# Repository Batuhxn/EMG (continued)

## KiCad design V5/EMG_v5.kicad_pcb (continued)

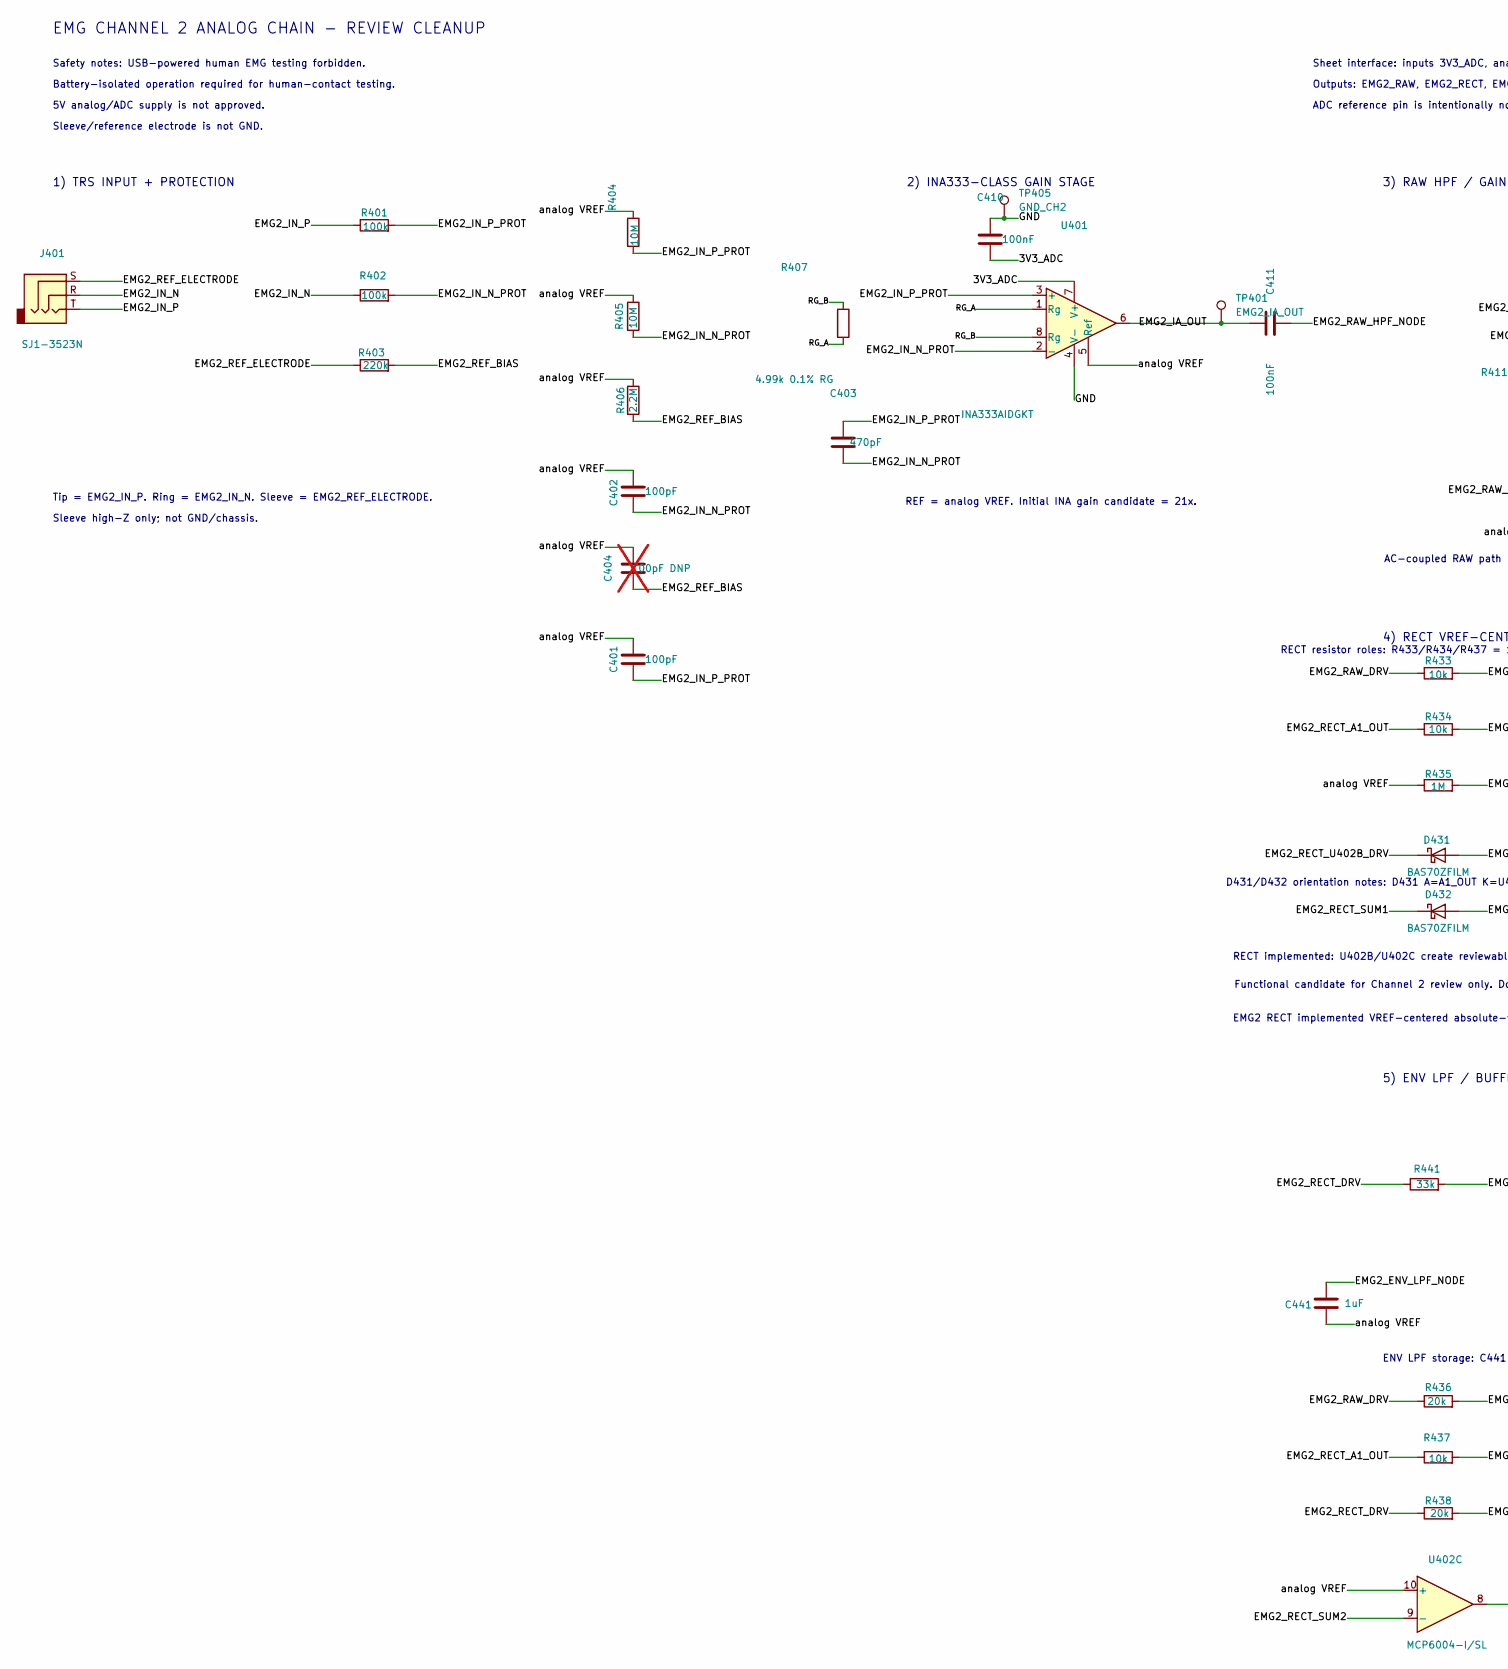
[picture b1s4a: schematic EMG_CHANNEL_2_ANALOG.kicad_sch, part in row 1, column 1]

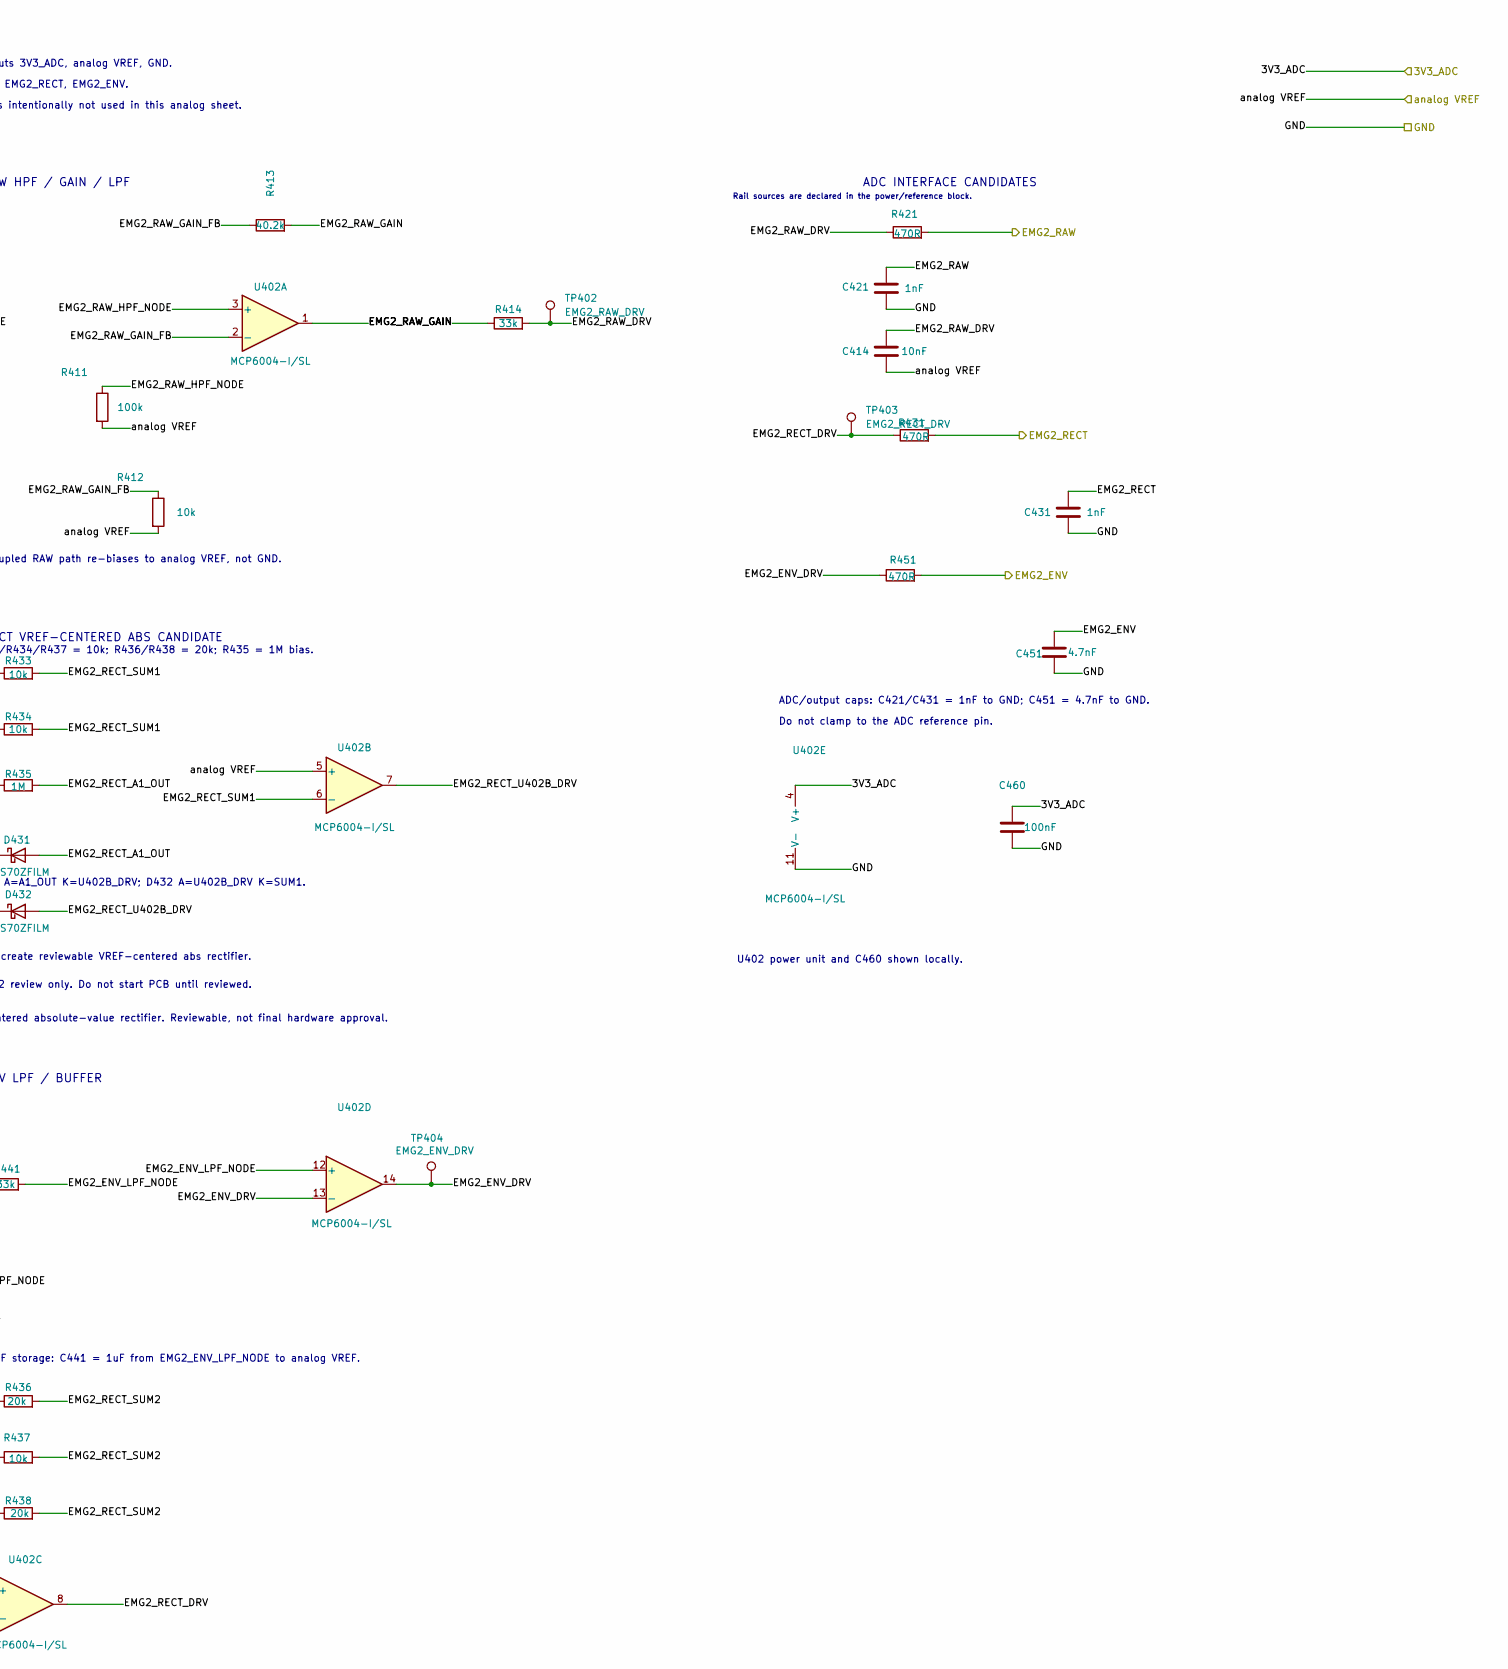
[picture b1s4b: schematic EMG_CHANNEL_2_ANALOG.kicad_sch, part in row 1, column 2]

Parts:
C401, C402: 100pF; C_0603_1608Metric
C403: 470pF; C_0603_1608Metric
C404: 100pF DNP; C_0603_1608Metric; not fitted
C410, C411: 100nF; C_0603_1608Metric
C414: 10nF; C_0603_1608Metric
C421, C431: 1nF; C_0805_2012Metric
C441: 1uF; C_0805_2012Metric
C451: 4.7nF; C_0805_2012Metric
C460: 100nF; C_0805_2012Metric
D431, D432: BAS70ZFILM; D_SOD-123
J401: SJ1-3523N; Jack_3.5mm_CUI_SJ1-3523N_Horizontal
R401, R402: 100k; R_1206_3216Metric
R403: 220k; R_1206_3216Metric
R404, R405: 10M; R_1206_3216Metric
R406: 2.2M; R_1206_3216Metric
R407: 4.99k 0.1% RG; R_0805_2012Metric
R411: 100k; R_0805_2012Metric
R412, R433, R434, R437: 10k; R_0805_2012Metric
R413: 40.2k; R_0805_2012Metric
R414, R441: 33k; R_0805_2012Metric
R421, R431, R451: 470R; R_0805_2012Metric
R435: 1M; R_0805_2012Metric
R436, R438: 20k; R_0805_2012Metric
TP401: EMG2_IA_OUT; TestPoint_Pad_D1.5mm
TP402: EMG2_RAW_DRV; TestPoint_Pad_D1.5mm
TP403: EMG2_RECT_DRV; TestPoint_Pad_D1.5mm
TP404: EMG2_ENV_DRV; TestPoint_Pad_D1.5mm
TP405: GND_CH2; TestPoint_Pad_D2.0mm
U401: INA333AIDGKT; INA333_DGK_VSSOP-8_TI
U402: MCP6004-I/SL; SOIC-14_3.9x8.7mm_P1.27mm

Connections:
/EMG_CHANNEL_1_ANALOG/3V3_ADC: C410.2, C460.1, U401.7 (V+), U402.4 (V+); also elsewhere on the board
/EMG_CHANNEL_1_ANALOG/analog VREF: C401.1, C402.1, C404.1, C414.2, C441.2, R404.1, R405.1, R406.1, R411.2, R412.2, R435.1, U401.5 (Ref), U402.5 (+), U402.10 (+); also elsewhere on the board
/EMG_CHANNEL_2_ANALOG/EMG2_ENV: C451.1, R451.2; also elsewhere on the board
/EMG_CHANNEL_2_ANALOG/EMG2_ENV_DRV: R451.1, TP404.1 (1_1), U402.13 (-), U402.14
/EMG_CHANNEL_2_ANALOG/EMG2_ENV_LPF_NODE: C441.1, R441.2, U402.12 (+)
/EMG_CHANNEL_2_ANALOG/EMG2_IA_OUT: C411.1, TP401.1 (1_1), U401.6
/EMG_CHANNEL_2_ANALOG/EMG2_IN_N: J401.R, R402.1
/EMG_CHANNEL_2_ANALOG/EMG2_IN_N_PROT: C402.2, C403.2, R402.2, R405.2, U401.2 (-)
/EMG_CHANNEL_2_ANALOG/EMG2_IN_P: J401.T, R401.1
/EMG_CHANNEL_2_ANALOG/EMG2_IN_P_PROT: C401.2, C403.1, R401.2, R404.2, U401.3 (+)
/EMG_CHANNEL_2_ANALOG/EMG2_RAW: C421.1, R421.2; also elsewhere on the board
/EMG_CHANNEL_2_ANALOG/EMG2_RAW_DRV: C414.1, R414.2, R421.1, R433.1, R436.1, TP402.1 (1_1)
/EMG_CHANNEL_2_ANALOG/EMG2_RAW_GAIN: R413.2, R414.1, U402.1
/EMG_CHANNEL_2_ANALOG/EMG2_RAW_GAIN_FB: R412.1, R413.1, U402.2 (-)
/EMG_CHANNEL_2_ANALOG/EMG2_RAW_HPF_NODE: C411.2, R411.1, U402.3 (+)
/EMG_CHANNEL_2_ANALOG/EMG2_RECT: C431.1, R431.2; also elsewhere on the board
/EMG_CHANNEL_2_ANALOG/EMG2_RECT_A1_OUT: D431.2 (A), R434.1, R435.2, R437.1
/EMG_CHANNEL_2_ANALOG/EMG2_RECT_DRV: R431.1, R438.1, R441.1, TP403.1 (1_1), U402.8
/EMG_CHANNEL_2_ANALOG/EMG2_RECT_SUM1: D432.1 (K), R433.2, R434.2, U402.6 (-)
/EMG_CHANNEL_2_ANALOG/EMG2_RECT_SUM2: R436.2, R437.2, R438.2, U402.9 (-)
/EMG_CHANNEL_2_ANALOG/EMG2_RECT_U402B_DRV: D431.1 (K), D432.2 (A), U402.7
/EMG_CHANNEL_2_ANALOG/EMG2_REF_BIAS: C404.2, R403.2, R406.2
/EMG_CHANNEL_2_ANALOG/EMG2_REF_ELECTRODE: J401.S, R403.1
/EMG_CHANNEL_2_ANALOG/RG_A: R407.2, U401.1 (Rg)
/EMG_CHANNEL_2_ANALOG/RG_B: R407.1, U401.8 (Rg)
GND: C410.1, C421.2, C431.2, C451.2, C460.2, TP405.1 (1_1), U401.4 (V-), U402.11 (V-); also elsewhere on the board

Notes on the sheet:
EMG CHANNEL 2 ANALOG CHAIN - REVIEW CLEANUP
Safety notes: USB-powered human EMG testing forbidden.
Battery-isolated operation required for human-contact testing.
5V analog/ADC supply is not approved.
Sleeve/reference electrode is not GND.
Sheet interface: inputs 3V3_ADC, analog VREF, GND.
Outputs: EMG2_RAW, EMG2_RECT, EMG2_ENV.
ADC reference pin is intentionally not used in this analog sheet.
Rail sources are declared in the power/reference block.
1) TRS INPUT + PROTECTION
Tip = EMG2_IN_P. Ring = EMG2_IN_N. Sleeve = EMG2_REF_ELECTRODE.
Sleeve high-Z only; not GND/chassis.
2) INA333-CLASS GAIN STAGE
REF = analog VREF. Initial INA gain candidate = 21x.
3) RAW HPF / GAIN / LPF
AC-coupled RAW path re-biases to analog VREF, not GND.
4) RECT VREF-CENTERED ABS CANDIDATE
RECT implemented: U402B/U402C create reviewable VREF-centered abs rectifier.
Functional candidate for Channel 2 review only. Do not start PCB until reviewed.
5) ENV LPF / BUFFER
ENV LPF storage: C441 = 1uF from EMG2_ENV_LPF_NODE to analog VREF.
U402 power unit and C460 shown locally.
ADC INTERFACE CANDIDATES
ADC/output caps: C421/C431 = 1nF to GND; C451 = 4.7nF to GND.
Do not clamp to the ADC reference pin.
D431/D432 orientation notes: D431 A=A1_OUT K=U402B_DRV; D432 A=U402B_DRV K=SUM1.
RECT resistor roles: R433/R434/R437 = 10k; R436/R438 = 20k; R435 = 1M bias.
EMG2 RECT implemented VREF-centered absolute-value rectifier. Reviewable, not final hardware approval.

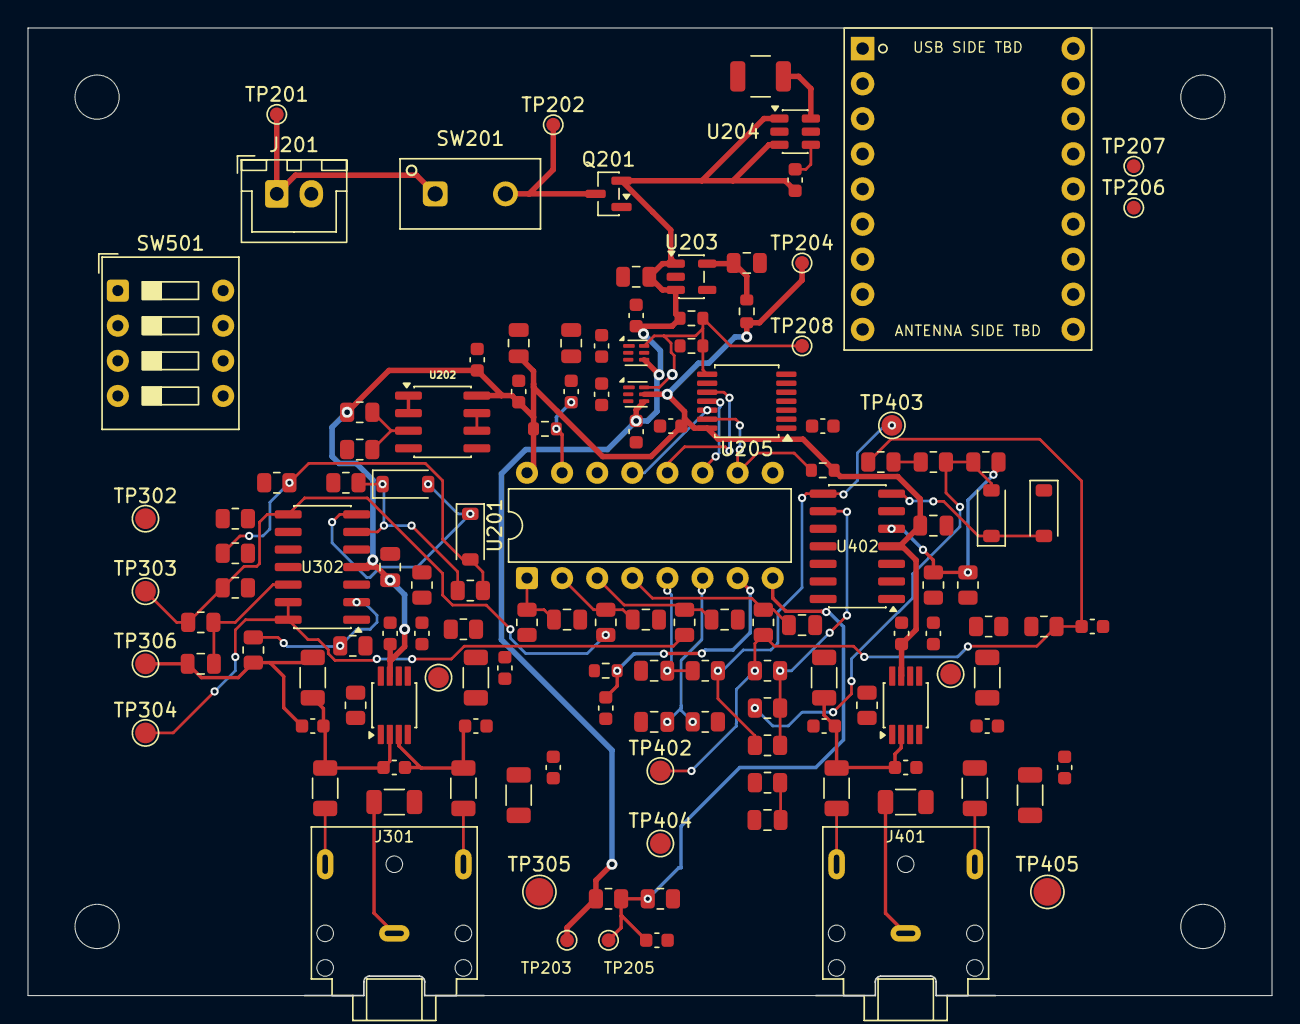
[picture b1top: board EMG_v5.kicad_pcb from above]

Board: 2 copper layers, 90.0 x 70.0 mm, 134 parts (0 on the bottom side), 76 nets.

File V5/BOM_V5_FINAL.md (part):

# EMG V5 Final Purchasing BOM

> Source of truth: `V5/EMG_v5.kicad_pcb` and related current schematics/documentation on branch `v5/KiCad`. Price/stock snapshot: **2026-08-10**. The old `BOM_V5_DRAFT.md` was used only as context; the current PCB wins on conflicts.

## Scope and totals

- **49 grouped purchasing lines**, **113 required populated components**, and **2 DNP components**.
- **C304/C404 are DNP**. Nineteen PCB test pads and four mounting-hole footprints are excluded from purchasing.
- Prototype component subtotal: **86.03 USD + 363.69 TRY**. Shipping, customs and non-row VAT are excluded; the U501 TRY price includes VAT.
- Recommended buy quantities include modest prototype spares. Recheck MOQ, multiples, Turkey-region stock, incoterms and landed cost in the final carts.

| Preferred distributor | Currency | BOM lines | Recommended units | Subtotal |
|---|:---:|---:|---:|---:|
| LCSC | USD | 22 | 152 | 1.44 |
| DigiKey | USD | 23 | 117 | 63.95 |
| Not purchased | USD | 1 | 0 | 0.00 |
| Mouser | USD | 2 | 4 | 20.64 |
| Direnc.net | TRY | 1 | 1 | 363.69 |

## Verification gates

- `BAS70ZFILM` is obsolete. The priced `1N5711W-7-F` candidate is SOD-123/70V/low-capacitance Schottky class, but analog clamp leakage, Vf and capacitance need bench sign-off.
- `PMV48XP,215` had no authorized stock in the checked sources. `FDN304P` is a stocked P-channel SOT-23 candidate; G/S/D mapping, RDS(on), gate charge and inrush behavior must be approved.
- `TPS22917DBVT` is a verified packaging-only substitute for the out-of-stock `TPS22917DBVR` and is the priced purchase choice.
- `U501` is verified only as local supplier SKU `DSTK22807`; manufacturer MPN and physical 2x9 board revision/pinout remain `TBD/Verify`.
- `SW501` procurement MPN `TDA04H0SB1R` matches the electrical/lead-grid class, but the body/courtyard still needs a mechanical overlay against the KiCad footprint.
- `J301/J401` use the requested `SJ1-3523N`. `C213` is the verified `GRM32ER71A476KE15L` (47uF, 10V, X7R, 1210).

## Full purchasing table

Prices are per unit in the stated currency. `Ext.` uses the recommended buy quantity.

| RefDes | Qty / req / buy | Value | Manufacturer / exact MPN | Package / mounting | DNP | Preferred / unit / ext. | Product links | Availability | Verified alternative / compatibility | Verification status |
|---|---:|---|---|---|:---:|---|---|---|---|---|
| C203,C205,C208,C214,C215,C216,C217,C310,C311,C410,C411 | 11 / 11 / 20 | 100nF | Murata Electronics<br>`GRM188R71C104KA01D` | 0603 (1608 metric), X7R, 16V, ±10%<br>SMD | No | LCSC<br>0.006814 USD<br>0.14 USD | [buy](https://www.lcsc.com/product-detail/C45000.html)<br>[second source](https://www.digikey.com/en/products/result?keywords=GRM188R7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 | LCSC C45000; 140,766 shown in stock. Recheck MOQ/multiple at checkout. | `CC0603KRX7R7BB104`<br>Same 0603/value/X7R class; verify voltage and DC-bias derating for the rail. | Verified – value, dielectric/tolerance and package matched; procurement MPN selected |
| C204,C206,C341,C441 | 4 / 4 / 10 | 1uF | Murata Electronics<br>`GRM21BR71C105KA01L` | 0805 (2012 metric), X7R, 16V, ±10%<br>SMD | No | DigiKey<br>0.14 USD<br>1.40 USD | [buy](https://www.digikey.com/en/products/detail/murata-electronic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 source](https://www.mouser.com/c/?q=GRM21BR71C105KA01L) | DigiKey listing active; large stock indicated. Price basis is low-quantity cut tape; recheck cart. | `GRM21BR71C105MA01K`<br>Same 0805/1uF/16V X7R; ±20% alternative is electrically broader, not preferred for critical tolerance. | Verified – value, dielectric/tolerance and package matched; procurement MPN selected |
| C207 | 1 / 1 / 5 | 220pF | Murata Electronics<br>`GRM1885C1H221JA01D` | 0603 (1608 metric), C0G/NP0, 50V, ±5%<br>SMD | No | DigiKey<br>0.12 USD<br>0.60 USD | [buy](https://www.digikey.com/en/products/detail/murata-electronic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 source](https://www.mouser.com/c/?q=GRM1885C1H221JA01D) | DigiKey showed 2,445 in stock; Murata part is NRND. Direct KEMET substitute available. | `C0603C221J5GACTU`<br>DigiKey-classified direct substitute; same 220pF ±5%, 50V, C0G, 0603. | Verified – exact part NRND; direct compatible alternative verified |
| C209,C210 | 2 / 2 / 5 | 2.2uF | Murata Electronics<br>`GRM21BR71A225KA01L` | 0805 (2012 metric), X7R, 10V, ±10%<br>SMD | No | DigiKey<br>0.18 USD<br>0.90 USD | [buy](https://www.digikey.com/en/products/detail/murata-electronic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 source](https://www.mouser.com/c/?q=GRM21BR71A225KA01L) | DigiKey showed 288,072 in stock; active. | `GRM21BR71C225KA12L`<br>Upgrade: same 0805/value/tolerance/X7R with higher 16V rating; drop-in. | Verified – value, dielectric/tolerance and package matched; procurement MPN selected |
| C211,C314,C414 | 3 / 3 / 10 | 10nF | Murata Electronics<br>`GRM188R71H103KA01D` | 0603 (1608 metric), X7R, 50V, ±10%<br>SMD | No | LCSC<br>0.003957 USD<br>0.04 USD | [buy](https://www.lcsc.com/product-detail/C77053.html)<br>[second source](https://www.digikey.com/en/products/result?keywords=GRM188R7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 | LCSC C77053; 248,887 shown in stock. Recheck MOQ/multiple. | `CC0603KRX7R9BB103`<br>Same 0603/value/X7R/50V class; drop-in after tolerance check. | Verified – value, dielectric/tolerance and package matched; procurement MPN selected |
| C212 | 1 / 1 / 5 | 2.2nF | Murata Electronics<br>`GRM1885C1H222JA01D` | 0603 (1608 metric), C0G/NP0, 50V, ±5%<br>SMD | No | LCSC<br>0.01 USD<br>0.06 USD | [buy](https://www.lcsc.com/product-detail/C77033.html)<br>[second source](https://www.digikey.com/en/products/result?keywords=GRM1885C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 | LCSC C77033; 24,839 shown in stock. C0G/NP0 selected for TPS22917 CT timing. | `C0603C222J5GACTU`<br>Same 0603/value/50V/C0G/±5%; drop-in. | Verified – value, dielectric/tolerance and package matched; procurement MPN selected |
| C213 | 1 / 1 / 2 | 47uF | Murata Electronics<br>`GRM32ER71A476KE15L` | 1210 (3225 metric), X7R, 10V, ±10%<br>SMD | No | LCSC<br>0.25 USD<br>0.51 USD | [buy](https://www.lcsc.com/product-detail/C84494.html)<br>[second source](https://www.digikey.com/en/products/detail/murata-electronic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 | LCSC C84494 showed 61,880 in stock. DigiKey exact part showed 10,818; $0.91 at qty 1. | `GRM32ER71C476KE15L`<br>Potential voltage upgrade only if exact height/DC-bias and availability are confirmed; verify before substitution. | Verified – exact requested MPN, 47uF/10V/X7R/1210 confirmed |
| C218,C219 | 2 / 2 / 5 | 9.1nF | Murata Electronics<br>`GCM1885C1H912GA16D` | 0603 (1608 metric), C0G/NP0, 50V, ±2%<br>SMD | No | DigiKey<br>0.17 USD<br>0.85 USD | [buy](https://www.digikey.com/en/products/detail/murata-electronic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 source](https://www.mouser.com/c/?q=GCM1885C1H912GA16D) | DigiKey showed 3,820 in stock; Mouser also showed >10k region stock. TME exact part was out of stock. | `GCM1885C1H912JA16D`<br>Same value/package/voltage/C0G with ±5% tolerance; use only if filter tolerance budget allows. | Verified – value, dielectric/tolerance and package matched; procurement MPN selected |
| C301,C302,C401,C402 | 4 / 4 / 10 | 100pF | Murata Electronics<br>`GRM1885C1H101JA01D` | 0603 (1608 metric), C0G/NP0, 50V, ±5%<br>SMD | No | LCSC<br>0.009400 USD<br>0.09 USD | [buy](https://www.lcsc.com/product-detail/C71664.html)<br>[second source](https://www.digikey.com/en/products/result?keywords=GRM1885C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 | LCSC C71664; 20,137 shown in stock. Recheck MOQ/multiple. | `C0603C101J5GACTU`<br>Same 0603/value/50V/C0G/±5%; drop-in. | Verified – value, dielectric/tolerance and package matched; procurement MPN selected |
| C303,C403 | 2 / 2 / 5 | 470pF | Murata Electronics<br>`GRM1885C1H471JA01D` | 0603 (1608 metric), C0G/NP0, 50V, ±5%<br>SMD | No | LCSC<br>0.005614 USD<br>0.03 USD | [buy](https://www.lcsc.com/product-detail/C85979.html)<br>[second source](https://www.digikey.com/en/products/result?keywords=GRM1885C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 | LCSC C85979; 25,277 shown in stock. Recheck MOQ/multiple. | `C0603C471J5GACTU`<br>Same 0603/value/50V/C0G/±5%; drop-in. | Verified – value, dielectric/tolerance and package matched; procurement MPN selected |
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
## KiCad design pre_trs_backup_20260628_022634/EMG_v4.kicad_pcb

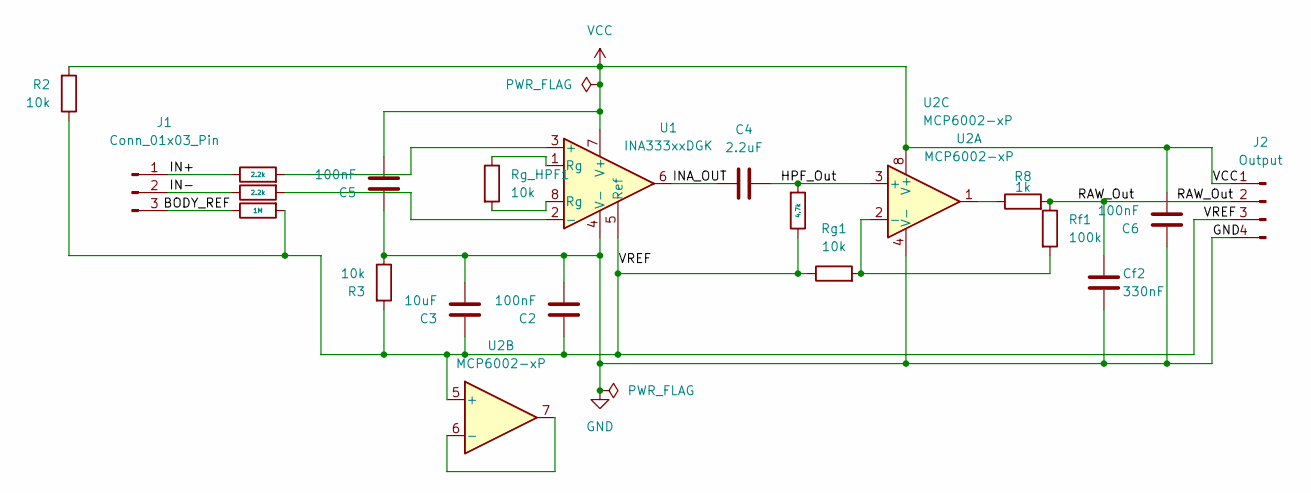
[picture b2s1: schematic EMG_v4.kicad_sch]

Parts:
C2, C5, C6: 100nF; C_Disc_D5.0mm_W2.5mm_P5.00mm
C3: 10uF; CP_Radial_D5.0mm_P2.50mm
C4: 2.2uF; C_Disc_D5.0mm_W2.5mm_P5.00mm
Cf2: 330nF; C_Disc_D5.0mm_W2.5mm_P5.00mm
J1: Conn_01x03_Pin; PinHeader_1x03_P2.54mm_Vertical
J2: Output; PinHeader_1x04_P2.54mm_Vertical
R2, R3: 10k; R_Axial_DIN0207_L6.3mm_D2.5mm_P7.62mm_Horizontal
R4, R5: 2.2k; R_Axial_DIN0207_L6.3mm_D2.5mm_P7.62mm_Horizontal
R6: 4.7k; R_Axial_DIN0207_L6.3mm_D2.5mm_P7.62mm_Horizontal
R7: 1M; R_Axial_DIN0207_L6.3mm_D2.5mm_P7.62mm_Horizontal
R8: 1k; R_Axial_DIN0207_L6.3mm_D2.5mm_P7.62mm_Horizontal
Rf1: 100k; R_Axial_DIN0207_L6.3mm_D2.5mm_P7.62mm_Horizontal
Rg1: 10k; R_Axial_DIN0207_L6.3mm_D2.5mm_P7.62mm_Horizontal
Rg_HPF1: 10k; R_Axial_DIN0207_L6.3mm_D2.5mm_P7.62mm_Horizontal
U1: INA333xxDGK; VSSOP-8_3x3mm_P0.65mm
U2: MCP6002-xP; DIP-8_W7.62mm

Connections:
/BODY_REF: J1.3, R7.1
/HPF_Out: C4.2, R6.2, U2.3 (+)
/IN+: J1.1, R4.1
/IN-: J1.2, R5.1
/INA_OUT: C4.1, U1.6
/RAW_Out: Cf2.2, J2.2, R8.2, Rf1.1
/VREF: C2.1, C3.1, J2.3, R2.1, R3.2, R6.1, R7.2, Rg1.1, U1.5 (Ref), U2.5 (+)
GND: C2.2, C3.2, C5.1, C6.1, Cf2.1, J2.4, R3.1, U1.4 (V-), U2.4 (V-)
unnamed: R8.1, U2.1
unnamed: Rg_HPF1.1, U1.1 (Rg)
unnamed: Rg_HPF1.2, U1.8 (Rg)
unnamed: R4.2, U1.3 (+)
unnamed: R5.2, U1.2 (-)
unnamed: Rf1.2, Rg1.2, U2.2 (-)
unnamed: U2.6 (-), U2.7
VCC: C5.2, C6.2, J2.1, R2.2, U1.7 (V+), U2.8 (V+)

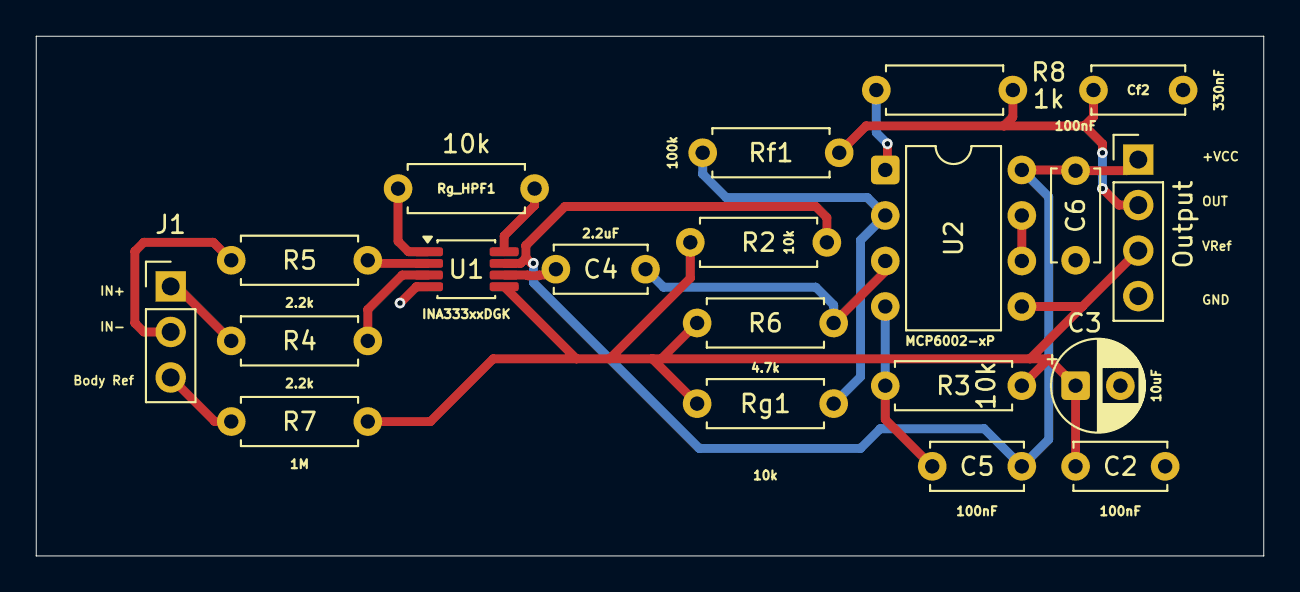
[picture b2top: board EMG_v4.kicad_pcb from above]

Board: 2 copper layers, 68.5 x 29.0 mm, 20 parts (0 on the bottom side), 16 nets.

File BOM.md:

# EMG Sensör v2 — Malzeme Listesi (BOM)

> Kart büyük ölçüde THT (delikli montaj) tasarımlıdır.
> Tek SMD bileşen U1 (INA333, VSSOP-8).

---

## Entegreler

| Ref | Değer | Paket | Adet | Nereden Alınır |
|-----|-------|-------|------|----------------|
| U1 | INA333AIDGKR | VSSOP-8 **SMD** | 1 | [direnc.net](https://www.direnc.net/ina333aidgkr-smd-amplifikator-entegre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 · [hepsiburada.com](https://www.hepsiburada.com/voltaj-ina333aidgkr-vssop-8-smd-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 |
| U2 | MCP6002-I/P | DIP-8 THT | 1 | [komponentci.net](https://www.komponentci.net/mcp6002-i-p-islemsel-amplifikato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 · [entegredunyasi.com.tr](https://www.entegredunyasi.com.tr/urun/mcp6002-i-p-pdip-8-op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 · [elektrodepo.com](https://www.elektrodepo.com/urun/mcp6002) · [ulutaselektronik.com](https://www.ulutaselektronik.com/urun/mcp6002-i-p-pdip-8-ope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 |

> **U1 UYARI:** INA333 VSSOP-8 çok küçük bir SMD paketidir (0.65mm pin adımı).
> El lehimlemesi için hot air veya ince uçlu havya + lehim pastası gerekir.
> İlk prototipi bir breakout board üzerinde kurmak kolaylık sağlar.

---

## Dirençler — Axial THT (1/4W yeterli)

| Ref | Değer | Adet | Nereden Alınır |
|-----|-------|------|----------------|
| Rg1, R2, R3 | 10 kΩ | 3 | [direnc.net](https://www.direnc.net/10k-direnc) · komponentci.net · herhangi lokal elektronikçi |
| R4, R5 | 2.2 kΩ | 2 | direnc.net · komponentci.net · lokal elektronikçi |
| R6 | 4.7 kΩ | 1 | direnc.net · komponentci.net · lokal elektronikçi |
| Rf1 | 100 kΩ | 1 | direnc.net · komponentci.net |
| Rg_HPF1 | 10 kΩ | 1 | direnc.net · komponentci.net · lokal elektronikçi |
| R7 | 1 MΩ | 1 | direnc.net · komponentci.net · lokal elektronikçi |

> Tüm dirençler çok yaygın değerler, herhangi bir lokal elektronikçide bulunur.

---

## Kondansatörler

| Ref | Değer | Paket | Adet | Nereden Alınır | Not |
|-----|-------|-------|------|----------------|-----|
| C2, C5, C6 | 100 nF | Disk seramik THT, 5mm adım | 3 | direnc.net · lokal elektronikçi | Standart bypass kap |
| C3 | 10 µF | Elektrolitik radial, D5×P2.5mm | 1 | [direnc.net](https://www.direnc.net/10-uf) · lokal elektronikçi | **Polarite önemli** |
| **C4** | **2.2 µF** | Film/polyester THT, **5mm adım** | 1 | direnc.net · komponentci.net | Aşağıdaki notu oku |
| Cf2 | 330 nF | Disk seramik / film THT, 5mm adım | 1 | direnc.net · komponentci.net | RAW_Out alçak geçiren filtre kondansatörü |

> **C4 NOTU:** Devrede iki ucu da yaklaşık VREF (VCC/2) potansiyelinde olduğu için
> **elektrolitik kullanma** — kutuplamalı çalışmaz veya bozulur.
> **Polyester film (MKT) 2.2µF 50V, 5mm adım** kullan.
> [direnc.net üzerinde "2.2uF film"](https://www.direnc.net/2-2uf-capacitor) veya
> Farnell Türkiye'den Vishay/WIMA MKT serisi ara.
> Bulamazsan 2.2µF **MLCC seramik** (X7R, 10V+) da olur ama bacak adımı farklı olabilir.

---

## Konektörler

| Ref | Değer | Paket | Adet | Nereden Alınır |
|-----|-------|-------|------|----------------|
| J1 | Pin Header 1×3 | 2.54mm pitch, dikey THT | 1 | direnc.net · robotistan.com · lokal |
| J2 | Pin Header 1×4 | 2.54mm pitch, dikey THT | 1 | direnc.net · robotistan.com · lokal |

---

## Önerilen Tedarikçiler (Türkiye)

| Site | Güçlü Olduğu Alan | URL |
|------|-------------------|-----|
| **direnc.net** | Genel pasifler, entegreler, geniş stok | https://www.direnc.net |
| **komponentci.net** | Entegreler, opamplar | https://www.komponentci.net |
| **entegredunyasi.com.tr** | Entegreler | https://www.entegredunyasi.com.tr |
| **elektrodepo.com** | Genel elektronik | https://www.elektrodepo.com |
| **ulutaselektronik.com** | Entegreler, pasifler | https://www.ulutaselektronik.com |
| **özdisan.com** | Profesyonel tedarik | https://www.ozdisan.com |
| **farnell (tr.farnell.com)** | Stok garantili, geniş seçim (kargo ücretli) | https://tr.farnell.com |
| **mouser.com.tr** | Tam stok, orijinal, uluslararası (kargo ücretli) | https://www.mouser.com.tr |

---

## Alım Sırası Önerisi

1. **Önce INA333'ü bul** — en zor bulunan, stok durumu değişken. direnc.net veya hepsiburada'ya bak. Yoksa Mouser'dan sipariş ver.
2. **MCP6002-I/P** — birden fazla sitede var, sorun olmaz.
3. **C4 (2.2µF film)** — elektrolitik değil film olmasına dikkat et.
4. **Geri kalan dirençler ve kaplar** — lokal herhangi bir elektronikçiden temin edilebilir.

---

*v2 — 2026-04-21*
